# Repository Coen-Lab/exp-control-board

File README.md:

# Experimental Control Board (ECB)
This repository houses the electronics, firmware, and enclosure design for the experimental control board. This board was designed by [Max Hunter](https://maxhunter.me/), to the specifications of Philip Coen. It  is designed both with features that are universally applicable to experimental neuroscience rigs, as well as some features which may not (but may) be useful outside the Coen Lab. In particular, the assembled board can be purchased at a comparable price to a _single component_ from a commercial supplier (e.g. this [current driver](https://www.thorlabs.com/thorproduct.cfm?partnumber=LEDD1B) or this [adjustable photodiode](https://www.thorlabs.com/thorproduct.cfm?partnumber=PDA8A2)). For most applications, this board can fully replace these components (in the enclosure of the current driver, it can replace 3 of them), amongst others.

If purchased directly from Max, the Version 3 board includes:
- 24V, 220W power supply
- Photodiode (2-pin)
- Temperature sensor (3-pin)
- Enclosure (Pink in above images)
- ECB Version 3 with the following features
	- Temperature-controlled PID Peltier cooler output with overheat protection
	- Two fixed 12V, 3A power rails for auxiliary devices, with switchable on/off outputs
	- Four variable 3-24V, 3A power rails for auxiliary devices, with switchable on/off outputs
	- Three adjustable 0-1A continuous current drivers for LEDs or similar devices
	- Photosensor with variable sensitivity trigger (5V TTL digital output)
	- Two DRV104 valve controllers, 12V output
	- One Arduino Nano V3, used to control Peltier output and random ‘flipper’ output, with 6 spare IO for future expansion

For useage instructions, please see:

[Version 3 documentation](Version3/README.md)

To purchase pre-assembled units, including photodiode etc. mentioned above, for ~£450 (at time of writing), please contact [Max Hunter](https://maxhunter.me/). 

All details are open source, and you can alternatively print your own boards: there is a folder of Gerbers and pick 'n place files for each version. However, please be aware that stock levels may necessitate equivalent-part subsitutions, so if you aren't familiar with ordering your own PCBs (e.g. you have no idea what Gerbers and pick 'n place files are), then we _strongly_ recommend you order pre-assembled units. Max may also be able to make minor design changes (for a design fee) if there are particular elements you would like added or removed.

&nbsp;
&nbsp;
This work is licensed under a
[Creative Commons Attribution-NonCommercial-ShareAlike 4.0 International License][cc-by-nc-sa].

[![CC BY-NC-SA 4.0][cc-by-nc-sa-image]][cc-by-nc-sa]

[cc-by-nc-sa]: http://creativecommons.org/licenses/by-nc-sa/4.0/
[cc-by-nc-sa-image]: https://licensebuttons.net/l/by-nc-sa/4.0/88x31.png
[cc-by-nc-sa-shield]: https://img.shields.io/badge/License-CC%20BY--NC--SA%204.0-lightgrey.svg

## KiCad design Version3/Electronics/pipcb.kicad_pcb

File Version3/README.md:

## ECB Version 3 guide and usage instructions

_Above_: Version 3 board CAD file (left) with both top and bottom of enclosure (centre) or just the bottom of the enclosure (right)

Thanks for purchasing (or considering) the ECB Version 3! This guide should act as a basic how-to to get started. If you have any questions/issues please post them on this github so that the entire community can benefit from the answers.

A purchasable Bill of Materials, all source code for the Arduino, a 3D-printable enclosure, and electronics design files can be found in this repository.

The board comes with a one-year warranty against manufacturing defects.

If you have any further questions or have any problems, please leave an issue on this GitHub repository.

## General notes
If purchased directly from Max, you have received:

- 24V, 220W power supply
- Photodiode (2-pin)
- Temperature sensor (3-pin)
- ECB Version 3 with the following features
    - Temperature-controlled PID Peltier cooler output with overheat protection
    - Two fixed 12V, 3A power rails for auxiliary devices, with switchable on/off outputs
    - Four variable 3-24V, 3A power rails for auxiliary devices, with switchable on/off outputs
    - Three adjustable 0-1A continuous current drivers for LEDs or similar devices
    - Photosensor with variable sensitivity trigger (5V TTL digital output)
    - Two DRV104 valve controllers, 12V output
    - One Arduino Nano V3, used to control Peltier output and random ‘flipper’ output, with 6 spare IO for future expansion

Please take the following precautions when handling the board.

* **At no point should you “hot-plug” / screw or unscrew anything into the board when it is powered on. The rapid transients caused by the making/breaking of contacts when screwing a cable in can damage the board as well as any attached components.**
* Do not overload or short-circuit any of the power rails.
* Please pay attention to the total maximum power rating of 220W, which is possible to exceed if fully loading all voltage rails.
* When handling or touching any components on the board, you should ground yourself with an ESD bracelet (£4 on Amazon) or by touching any grounded surface to dissipate electrostatic charge. Humans can accumulate several thousand volts of static charge which will dissipate through the board: several of the components on the board are very sensitive to ESD. When screwing in any of the terminals, take the same precaution, or use an insulated screwdriver so your skin does not make contact with the screw of the terminal.

## Installation/operation instructions

### General notes on screw terminals
All the external connections to the board are made using screw terminals. These accept a wide variety of wire sizes. You should strip 5mm off the wire, then unscrew the terminal until the jaws fully open, insert the wire, and hand-tighten. The screw should clamp down on the conductor (not the insulation) and no conductor should be visible out the end of the connector.

For low-power devices with small cable sizes it is acceptable to insert several wires into a single terminal, as long as they are all sufficiently stripped so that they are making good contact with the terminal.

### Enclosure
Four self-tapping screws can be inserted into the four corners of the enclosure in the pre-drilled holes to mount onto any suitable surface. The board can be installed in any orientation but preferably should be kept away from direct sunlight and heat sources.

### Power in

The board comes with a switchmode 24V, 220W power supply. You should sum up all the power ratings of the various attached devices (including Peltier cooler) and make sure they do not exceed 220W.

Once in the correct position, the insulation on the power connector should be cut off and the ends stripped to 5mm. Slightly twist the copper to make sure no strands splay off, then insert BLACK into ⏚ and RED into +24.

### Power out

There are 6 power rails for auxiliary devices on this board. All of them share the same 3A current rating.

RAIL 1: 12V fixed

RAIL 2: 12V fixed

RAIL 3: Variable 3-23V

RAIL 4: Variable 3-23V

RAIL 5: Variable 3-23V

RAIL 6: Variable 3-23V

RAIL 3-6 are adjustable by turning the potentiometers (blue cuboids) next to the relevant rails with a small insulated flat screwdriver, whilst metering the output voltage with the serial logger on the Arduino, or a multimeter. Care should be taken to make sure the screwdriver does not slip and you do not touch any other components while metering, especially if using a multimeter.

All rails have a GATE input. Leaving this pin disconnected, or connecting this to a voltage below approximately 1.3 V, turns the regulator on, and pulling this pin above 1.3 V (up to a maximum of 25 V) shuts the regulator down. This is a useful feature if you wish to use an Arduino pin (or other logic pin) to switch power to an external component. (Note that there are output capacitors on the voltage rails so the power will not switch off instantly)

### Peltier

This board is tested and designed to work with the following 24V, 60W Peltier cooling module: [https://uk.rs-online.com/web/p/heat-pumps/7777079](https://uk.rs-online.com/web/p/heat-pumps/7777079). Other modules may work, as long as they are 24V and do not exceed 8A.

Insert BLACK into ⏚ and RED into PELT.

Connect overheat switch to any terminal marked ⏚ and OHT (polarity does not matter). This is a NC (normally closed) design which opens if the Peltier overheats - if your Peltier unit does not have an overheat sensor you should either modify the Arduino code or put a small bit of wire between OHT and ⏚ to bypass it.

The temperature sensor (mandatory for Peltier cooling) should be plugged into T SENSOR. Red into +5, yellow into D (data), black into ⏚. It should be positioned close to/underneath the desired position to be kept at a constant temperature.

The two fans (if available) should be plugged into any +12V rail.

The code for the Peltier follows a PID loop with a frequency of approximately 800KHz. It is roughly tuned for The Coen Lab’s original experimental box and so the P, I, D constants may need adjusting if the temperature proves to oscillate or under/overshoot in a new environment or with a different Peltier.

### Photodiode

This is a completely separate module from the rest of the board, designed as an adjustable photodiode trigger at a user-settable light threshold - originally designed to be placed next to a square on a screen to synchronise it with experimental data. This turns a variable light level into a digital 5V TTL logic output. There is a Schmitt trigger to remove hysteresis. The included photodiode (optional) should be plugged with the RED wire into S- and the BLUE wire into S+. The photodiode should be placed in the desired position and the potentiometer adjusted for the desired sensitivity.

The output between OUT and ⏚ is the 5V TTL out. The output between RAW and ⏚ is designed as an ‘analogue backup’ in case the sensitivity is slightly wrong - it is an analogue voltage (controlled by the SENSITIVITY  knob) before the Schmitt comparator where 2.5V is approximately the midpoint threshold.

### Valve drivers

These are 2 completely independent valve drivers. They take 5V TTL logic in (between IN and ⏚) and connect to a valve. The specs are fixed and as follows:

This was designed for the following valve:

225P011-21 ([https://www.nresearch.com/products/valves/pinch-1xnc.html](https://www.nresearch.com/products/valves/pinch-1xnc.html))

When the logic level input goes above approximately 2.2V (maximum 5.5V) the output briefly rises to 12V for 100ms, then continues to pulse between 0V and 12V at a 33% duty cycle until the input voltage drops beneath approximately 1.2V. This keeps the valve open without burning out the solenoid.

### Constant current drivers
\
\

There are 3 constant-current drivers on this board. They are adjustable in 3 fixed steps: 333mA, 667mA, 1000mA, by adding or removing jumpers on the board as shown.

They can also be controlled with the CTL pin for the relevant output as follows:

0-2.5V: scales linearly between 0A and the maximum set current (i.e. if the jumpers are set to 1A, setting the CTL pin at 1.25V will output a target current of 500mA).

2.5-5V: fully ON.

This can be used either as analogue control from 0-2.5V, or as a digital on/off switch by modulating the input voltage between 0 and 5V.

There is an internal pull-up resistor, so leaving this pin floating is the same as pulling it up to +5V (ie "on").

### Arduino I/O
\

This is a breakout board for the included Arduino Nano v3. 

The implemented features in the provided firmware are:

A ‘flipper’ random I/O which randomly flips between HIGH and LOW approximately every 100ms. This is turned on and off by setting FE (flipper enable) to HIGH or LOW.

An OHT overheat sensor for the Peltier (described in the Peltier section above)

Two ⏚ ground terminals and a 5V logic output. This 5V output is a logic reference only and not to be used for power. Drawing more than 50mA of current through it will result in permanent damage to the board. If there is any chance of it shorting to ground (or any other voltage), a 200 ohm resistor in series with it is strongly recommended.

The other outputs match the Arduino pinout and are reserved for future expansion.

Plugging the board into a computer is optional and only needed if you wish to log temperature/rail voltages etc, or update the firmware.

The firmware is available on GitHub and can be modified and uploaded using the connector on the Arduino. Plugging in the USB-C connector and opening up the serial logger on the Arduino app (or a MATLAB/Python program) will print rail voltages and temperature. You can then use the Arduino app to reflash any firmware changes.

## Manufacturing instructions

### Board

A service like JLCPCB can be used with the included Gerber and pick&place files to manufacture and assemble the board.

### Enclosure

Pip Coen has designed a 3D-printable enclosure which can be found in this repository.

The enclosure is designed to take 8 regular M4 nuts and M4 bolts.

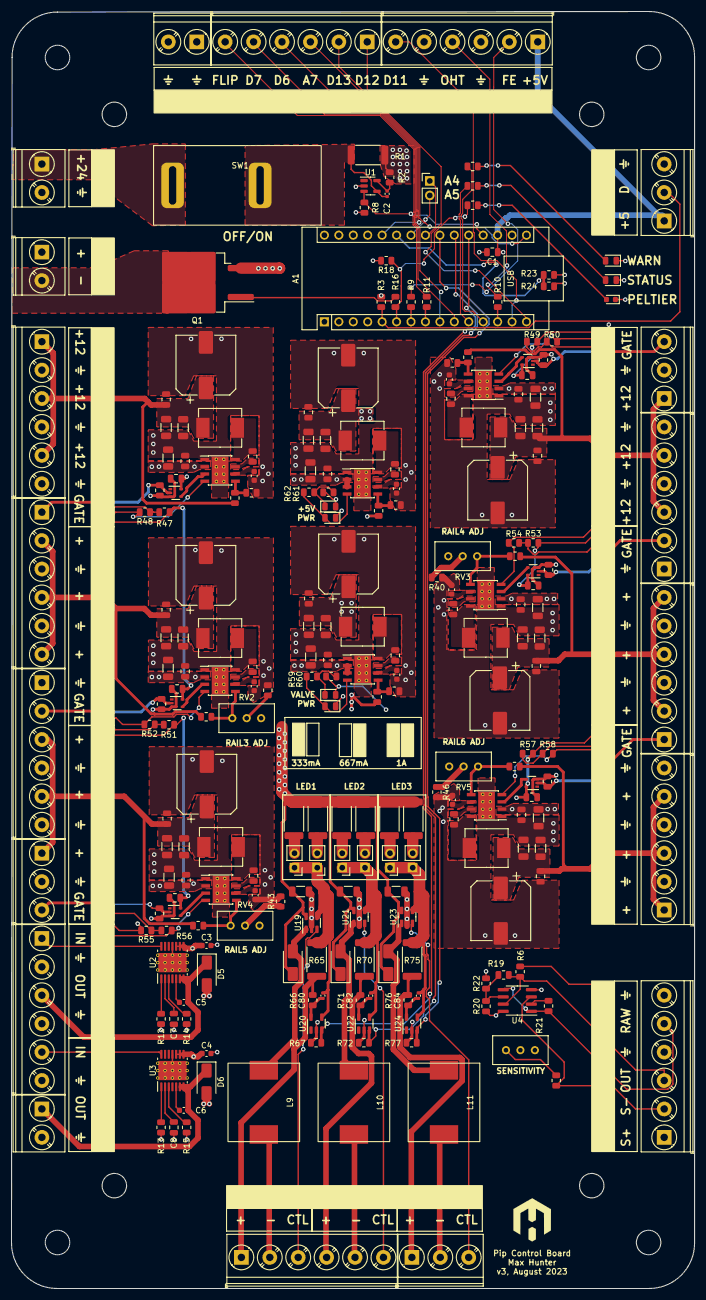
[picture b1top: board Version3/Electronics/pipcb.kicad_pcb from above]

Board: 4 copper layers, 120.2 x 224.7 mm, 272 parts (0 on the bottom side), 148 nets.

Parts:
A1: Arduino_Nano_v3.x; Arduino_Nano
C1, C9, C10, C11, C12, C13, C14, C18, C26, C34, C42, C50, C58, C66, C74: 100n; C_0805_2012Metric
C2, C80, C82, C84: 10p; C_0402_1005Metric
C3, C4, C22, C30, C38, C46, C54, C62, C70, C78: 1u; C_0603_1608Metric
C5, C6: 470p; C_0603_1608Metric
C7, C8: 150n; C_0805_2012Metric
C15, C19, C20, C23, C27, C28, C31, C35, C36, C39, C43, C44, C47, C51, C52, C55, C59, C60, C63, C67, C68, C71, C75, C76, C79, C81, C83: 10u; C_1206_3216Metric
C16, C17, C24, C25, C32, C33, C40, C41, C48, C49, C56, C57, C64, C65, C72, C73: 220n; C_0805_2012Metric
C21, C29, C37, C45, C53, C61, C69, C77: 100u; CP_Elec_10x10
D1, D7, D9, D11, D13, D15, D17, D19, D21: RED; LED_0805_2012Metric
D2: YELLOW; LED_0805_2012Metric
D3, D8, D10, D12, D14, D16, D18, D20, D22: GREEN; LED_0805_2012Metric
D4: BLUE; LED_0603_1608Metric
D5, D6, D23, D24, D25: SS34; D_SMA
G1: LOGO; maxlogo
H1, H2, H3, H4, H5, H6, H7, H8: MountingHole; MountingHole_4.3mm_M4
J1, J2, J4, J5, J7, J8, J12, J14, J15, J17, J19: Conn_01x06; TerminalBlock_Phoenix_PT-1,5-6-5.0-H_1x06_P5.00mm_Horizontal
J3, J6, J16, J18: Conn_01x02; TerminalBlock_Phoenix_PT-1,5-2-5.0-H_1x02_P5.00mm_Horizontal
J9: Conn_01x02; PinHeader_1x02_P2.54mm_Vertical
J10, J11, J13, J20: Conn_01x03; TerminalBlock_Phoenix_PT-1,5-3-5.0-H_1x03_P5.00mm_Horizontal
J21, J22: Conn_01x15; DOT
JP1, JP2, JP3, JP4, JP5, JP6: JUMP; PinHeader_1x02_P2.54mm_Vertical
JP7, JP8, JP9, JP10, JP11, JP12: Jumper_2_Bridged; DOT
L1, L2, L3, L4, L5, L6, L7, L8: 15uH 4A; L_Cenker_CKST0603
L9, L10, L11: 100uH; L_SMMS1360
Q1: LNE08R085; TO-263-2
R1, R65, R70, R75: 0.005R; R_2512_6332Metric
R2, R3, R66, R71, R76: 4.7k; R_0805_2012Metric
R4, R5, R9, R10, R11, R16: 220R; R_0805_2012Metric
R6, R7: 1k; R_0805_2012Metric
R8, R67, R72, R77: 13k; R_0805_2012Metric
R12, R13: 120k; R_0805_2012Metric
R14, R15: 200k; R_0805_2012Metric
R17, R18, R21: 10k; R_0805_2012Metric
R19: 150k; R_0805_2012Metric
R20, R22: 30k; R_0805_2012Metric
R23, R27, R32, R36, R39, R42, R45: 47k 1%; R_0805_2012Metric
R24: 8.87k 1%; R_0805_2012Metric
R25, R28, R30, R33, R35, R38, R41, R44: 100k 1%; R_0805_2012Metric
R26, R29, R31: 9.09k 1%; R_0805_2012Metric
R34: 24.9k 1%; R_0805_2012Metric
R37, R40, R43, R46: 4.3k; R_0805_2012Metric
R47, R49, R51, R53, R55, R57, R59, R61: 470R; R_0805_2012Metric
R48, R50, R52, R54, R56, R58, R60, R62: 560R; R_0805_2012Metric
R63, R68, R73: 0.15R; R_2512_6332Metric
R64, R69, R74: 0.3R; R_2512_6332Metric
RV2, RV3, RV4, RV5: 47k 10-turn; Potentiometer_Bourns_3296W_Vertical
SW1: C3900BAAAA
U1, U20, U22, U24: ZXCT1110; SOT-23-5
U2, U3: DRV104; HTSSOP-14-1EP_4.4x5mm_P0.65mm_EP3.4x5mm_Mask3x3.1mm_Thermal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
U4: MCP6002-xSN; SOIC-8_3.9x4.9mm_P1.27mm
U5, U6, U7, U8, U9, U10: 74LVC1G04; SOT-353_SC-70-5
U11, U12, U13, U14, U15, U16, U17, U18: LMR33630ADDA; Texas_HSOP-8-1EP_3.9x4.9mm_P1.27mm_ThermalVias
U19, U21, U23: AL8861WT-7; TSOT-23-5
locked: 5M; Potentiometer_Bourns_3296W_Vertical

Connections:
5V_PG: D22.2 (A), R62.2, U18.4 (PG)
24_V_ADC: A1.25 (A6), R23.1, R24.2
+24V: C15.1, C16.1, C23.1, C24.1, C31.1, C32.1, C39.1, C40.1, C47.1, C48.1, C55.1, C56.1, C63.1, C64.1, C71.1, C72.1, C79.1, C81.1, C83.1, D23.1 (K), D24.1 (K), D25.1 (K), J6.1, R1.1, R2.2, R23.2, R63.1, R64.1, R68.1, R69.1, R73.1, R74.1, U11.2 (VIN), U12.2 (VIN), U13.2 (VIN), U14.2 (VIN), U15.2 (VIN), U16.2 (VIN), U17.2 (VIN), U17.3 (EN), U18.2 (VIN), U18.3 (EN), U19.5 (VIN), U21.5 (VIN), U23.5 (VIN)
+VDC: J3.1, SW1.1 (A)
/power_rails/5v_pwr/FB: R33.2, R34.1, U18.5 (FB)
/power_rails/rail1/FB: R25.2, R26.1, U11.5 (FB)
/power_rails/rail1/RAIL_EN: U5.4, U11.3 (EN)
/power_rails/rail2/FB: R30.2, R31.1, U12.5 (FB)
/power_rails/rail2/RAIL_EN: U6.4, U12.3 (EN)
/power_rails/rail3/FB: R35.2, RV2.3, U13.5 (FB)
/power_rails/rail3/RAIL_EN: U7.4, U13.3 (EN)
/power_rails/rail4/FB: R38.2, RV3.3, U14.5 (FB)
/power_rails/rail4/RAIL_EN: U8.4, U14.3 (EN)
/power_rails/rail5/FB: R41.2, RV4.3, U15.5 (FB)
/power_rails/rail5/RAIL_EN: U9.4, U15.3 (EN)
/power_rails/rail6/FB: R44.2, RV5.3, U16.5 (FB)
/power_rails/rail6/RAIL_EN: U10.4, U16.3 (EN)
/power_rails/valve_12v_pwr/FB: R28.2, R29.1, U17.5 (FB)
CURRENT_ADC: A1.19 (A0), R8.2, U1.3 (OUT)
FLIPPER_ENABLE: A1.7 (D4), R9.2
FLIPPER_OUT: A1.8 (D5), R11.2
GND: A1.4 (GND), A1.29 (GND), C1.2, C3.2, C4.2, C7.2, C8.2, C9.2, C10.2, C11.2, C12.2, C13.2, C14.2, C15.2, C16.2, C18.2, C19.2, C20.2, C21.2, C22.2, C23.2, C24.2, C26.2, C27.2, C28.2, C29.2, C30.2, C31.2, C32.2, C34.2, C35.2, C36.2, C37.2, C38.2, C39.2, C40.2, C42.2, C43.2, C44.2, C45.2, C46.2, C47.2, C48.2, C50.2, C51.2, C52.2, C53.2, C54.2, C55.2, C56.2, C58.2, C59.2, C60.2, C61.2, C62.2, C63.2, C64.2, C66.2, C67.2, C68.2, C69.2, C70.2, C71.2, C72.2, C74.2, C75.2, C76.2, C77.2, C78.2, C79.2, C81.2, C83.2, D1.1 (K), D2.1 (K), D3.1 (K), D4.1 (K), D5.2 (A), D6.2 (A), D8.1 (K), D10.1 (K), D12.1 (K), D14.1 (K), D16.1 (K), D18.1 (K), D20.1 (K), D22.1 (K), J1.2, J1.4, J1.6, J2.2, J2.4, J2.6, J3.2, J4.3, J4.5, J5.3, J5.5, J7.1, J7.4, J7.6, J8.1, J8.4, J8.6, J10.2, J11.2, J12.4, J12.6, J13.3, J14.2, J14.4, J14.6, J15.3, J15.5, J16.2, J18.1, J18.2, Q1.3 (S), R8.1, R12.2, R13.2, R14.2, R15.2, R18.2, R22.2, R24.1, R26.2, R27.1, R29.2, R31.2, R32.1, R34.2, R36.1, R37.2, R39.1, R40.2, R42.1, R43.2, R45.1, R46.2, R67.1, R72.1, R77.1, U1.2 (GND), U2.11 (GND), U2.15 (PPAD), U3.11 (GND), U3.15 (PPAD), U4.4 (V-), U5.3 (GND), U6.3 (GND), U7.3 (GND), U8.3 (GND), U9.3 (GND), U10.3 (GND), U11.1 (PGND), U11.9 (AGND), U12.1 (PGND), U12.9 (AGND), U13.1 (PGND), U13.9 (AGND), U14.1 (PGND), U14.9 (AGND), U15.1 (PGND), U15.9 (AGND), U16.1 (PGND), U16.9 (AGND), U17.1 (PGND), U17.9 (AGND), U18.1 (PGND), U18.9 (AGND), U19.2 (GND), U20.2 (GND), U21.2 (GND), U22.2 (GND), U23.2 (GND), U24.2 (GND), locked.2, locked.3
GPIO1: A1.14 (D11), J15.6
GPIO2: A1.15 (D12), J17.1
GPIO3: A1.16 (D13), J17.2
GPIO4: A1.26 (A7), J17.3
GPIO5: A1.9 (D6), J17.4
GPIO6: A1.10 (D7), J17.5
LED1_CONTROL: J19.3, U19.3 (VSET)
LED1_CURR: A1.20 (A1), R67.2, U20.3 (OUT)
LED1_OUT+: J19.1, R65.1, R66.2
LED1_OUT-: J19.2, L9.2
LED2_CONTROL: J19.6, U21.3 (VSET)
LED2_CURR: A1.21 (A2), R72.2, U22.3 (OUT)
LED2_OUT+: J19.4, R70.1, R71.2
LED2_OUT-: J19.5, L10.2
LED3_CONTROL: J20.3, U23.3 (VSET)
LED3_CURR: A1.22 (A3), R77.2, U24.3 (OUT)
LED3_OUT+: J20.1, R75.1, R76.2
LED3_OUT-: J20.2, L11.2
LED_STATUS: A1.11 (D8), R5.2
LED_WARNING: A1.12 (D9), R4.2
unnamed: A1.23 (A4), J9.1
unnamed: A1.24 (A5), J9.2
unnamed: D1.2 (A), R4.1
unnamed: D2.2 (A), R5.1
unnamed: D3.2 (A), R6.1
unnamed: D4.2 (A), R7.1
unnamed: D7.1 (K), R47.1, R48.1
unnamed: D9.1 (K), R49.1, R50.1
unnamed: D11.1 (K), R51.1, R52.1
unnamed: D13.1 (K), R53.1, R54.1
unnamed: D15.1 (K), R55.1, R56.1
unnamed: D17.1 (K), R57.1, R58.1
unnamed: D19.1 (K), R59.1, R60.1
unnamed: D21.1 (K), R61.1, R62.1
unnamed: D23.2 (A), L9.1, U19.1 (LX)
unnamed: D24.2 (A), L10.1, U21.1 (LX)
unnamed: D25.2 (A), L11.1, U23.1 (LX)
unnamed: J15.2, R9.1
unnamed: J15.4, R10.1
unnamed: J17.6, R11.1
unnamed: C80.2, JP1.1 (A), JP2.1 (A), R65.2, U19.4 (ISENSE), U20.4 (Vs+)
unnamed: JP1.2 (B), R63.2
unnamed: JP2.2 (B), R64.2
unnamed: C82.2, JP3.1 (A), JP4.1 (A), R70.2, U21.4 (ISENSE), U22.4 (Vs+)
unnamed: JP3.2 (B), R68.2
unnamed: JP4.2 (B), R69.2
unnamed: C84.2, JP5.1 (A), JP6.1 (A), R75.2, U23.4 (ISENSE), U24.4 (Vs+)
unnamed: JP5.2 (B), R73.2
unnamed: JP6.2 (B), R74.2
unnamed: Q1.1 (G), R16.1
unnamed: R17.2, locked.1
unnamed: R37.1, RV2.2
unnamed: R40.1, RV3.2
unnamed: R43.1, RV4.2
unnamed: R46.1, RV5.2
unnamed: C2.2, R1.2, SW1.2 (B), U1.4 (Vs+)
unnamed: C2.1, R2.1, U1.5 (Vs-)
unnamed: C5.2, U2.5 (BOOT)
unnamed: C7.1, U2.2 (DELAY_ADJ)
unnamed: R12.1, U2.1 (DUTY_ADJ)
unnamed: R14.1, U2.3 (OSC_ADJ)
unnamed: C6.2, U3.5 (BOOT)
unnamed: C8.1, U3.2 (DELAY_ADJ)
unnamed: R13.1, U3.1 (DUTY_ADJ)
unnamed: R15.1, U3.3 (OSC_ADJ)
unnamed: R21.2, U4.2 (-)
unnamed: R19.2, R20.2, R22.1, U4.6 (-)
unnamed: C17.2, U11.7 (BOOT)
unnamed: C17.1, L1.1, U11.8 (SW)
unnamed: C22.1, U11.6 (VCC)
unnamed: C25.2, U12.7 (BOOT)
unnamed: C25.1, L2.1, U12.8 (SW)
unnamed: C30.1, U12.6 (VCC)
unnamed: C33.2, U13.7 (BOOT)
unnamed: C33.1, L3.1, U13.8 (SW)
unnamed: C38.1, U13.6 (VCC)
unnamed: C41.2, U14.7 (BOOT)
unnamed: C41.1, L4.1, U14.8 (SW)
unnamed: C46.1, U14.6 (VCC)
unnamed: C49.2, U15.7 (BOOT)
unnamed: C49.1, L5.1, U15.8 (SW)
unnamed: C54.1, U15.6 (VCC)
unnamed: C57.2, U16.7 (BOOT)
unnamed: C57.1, L6.1, U16.8 (SW)
unnamed: C62.1, U16.6 (VCC)
unnamed: C65.2, U17.7 (BOOT)
unnamed: C65.1, L7.1, U17.8 (SW)
unnamed: C70.1, U17.6 (VCC)
unnamed: C73.2, U18.7 (BOOT)
unnamed: C73.1, L8.1, U18.8 (SW)
unnamed: C78.1, U18.6 (VCC)
unnamed: C80.1, R66.1, U20.5 (Vs-)
unnamed: C82.1, R71.1, U22.5 (Vs-)
unnamed: C84.1, R76.1, U24.5 (Vs-)
OVERHEAT: A1.13 (D10), R10.2
PELTIER_CONTROL: A1.6 (D3), R7.2, R16.2, R18.1
PELTIER_OUT: J6.2, Q1.2 (D)
PS_1: A1.18 (AREF), A1.27 (+5V), C1.1, C9.1, C10.1, C11.1, C12.1, C13.1, C14.1, C74.1, C75.1, C76.1, C77.1, D7.2 (A), D9.2 (A), D11.2 (A), D13.2 (A), D15.2 (A), D17.2 (A), D19.2 (A), D21.2 (A), J12.1, J13.1, J15.1, L8.2, R3.1, R20.1, R33.1, R47.2, R49.2, R51.2, R53.2, R55.2, R57.2, R59.2, R61.2, U4.8 (V+), U5.5 (VCC), U6.5 (VCC), U7.5 (VCC), U8.5 (VCC), U9.5 (VCC), U10.5 (VCC)
PS_2: J12.2, R17.1, U4.3 (+)
PS_RAW_OUT: J12.5, R21.1, U4.1, U4.5 (+)
PS_TRIGGER: J12.3, R6.2, R19.1, U4.7
RAIL1+: C18.1, C19.1, C20.1, C21.1, J2.1, J2.3, J2.5, L1.2, R25.1
RAIL1_EN: J5.1, R27.2, U5.2
RAIL1_PG: D8.2 (A), R48.2, U11.4 (PG)
RAIL2+: C26.1, C27.1, C28.1, C29.1, J7.3, J7.5, J10.1, L2.2, R30.1
RAIL2_EN: J10.3, R32.2, U6.2
RAIL2_PG: D10.2 (A), R50.2, U12.4 (PG)
RAIL3+: C34.1, C35.1, C36.1, C37.1, J5.2, J5.4, J5.6, L3.2, R35.1
RAIL3_EN: J8.2, R36.2, U7.2
RAIL3_PG: D12.2 (A), R52.2, U13.4 (PG)
RAIL4+: C42.1, C43.1, C44.1, C45.1, J4.2, J4.4, J4.6, L4.2, R38.1
RAIL4_EN: J7.2, R39.2, U8.2
RAIL4_PG: D14.2 (A), R54.2, U14.4 (PG)
RAIL5+: C50.1, C51.1, C52.1, C53.1, J8.3, J8.5, J11.1, L5.2, R41.1
RAIL5_EN: J11.3, R42.2, U9.2
RAIL5_PG: D16.2 (A), R56.2, U15.4 (PG)
RAIL6+: C58.1, C59.1, C60.1, C61.1, J1.1, J1.3, J1.5, L6.2, R44.1
RAIL6_EN: J4.1, R45.2, U10.2
RAIL6_PG: D18.2 (A), R58.2, U16.4 (PG)
TEMP_SENSOR: A1.5 (D2), J13.2, R3.2
VALVE1_IN: J14.1, U2.14 (INPUT)
VALVE1_OUT: C5.1, D5.1 (K), J14.3, U2.6 (OUT1), U2.7 (OUT2)
VALVE2_IN: J14.5, U3.14 (INPUT)
VALVE2_OUT: C6.1, D6.1 (K), J16.1, U3.6 (OUT1), U3.7 (OUT2)
VALVE_12V: C3.1, C4.1, C66.1, C67.1, C68.1, C69.1, L7.2, R28.1, U2.8 (VPS1), U2.9 (VPS2), U2.10 (+VS), U3.8 (VPS1), U3.9 (VPS2), U3.10 (+VS)
VALVE_PG: D20.2 (A), R60.2, U17.4 (PG)

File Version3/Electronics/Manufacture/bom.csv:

Designator,Footprint,Quantity,Value,LCSC Part #
A1,Arduino_Nano,1,Arduino_Nano_v3.x,
"C1, C10, C11, C12, C13, C14, C18, C26, C34, C42, C50, C58, C66, C74, C9",0805,15,100n,C28233
"C15, C19, C20, C23, C27, C28, C31, C35, C36, C39, C43, C44, C47, C51, C52, C55, C59, C60, C63, C67, C68, C71, C75, C76, C79, C81, C83",1206,27,10u,C13585
"C16, C17, C24, C25, C32, C33, C40, C41, C48, C49, C56, C57, C64, C65, C72, C73",0805,16,220n,C5378
"C2, C80, C82, C84",0402,4,10p,C32949
"C21, C29, C37, C45, C53, C61, C69, C77",CP_Elec_10x10,8,100u,C371283
"C22, C3, C30, C38, C4, C46, C54, C62, C70, C78",0603,10,1u,C15849
"C5, C6",0603,2,470p,C1620
"C7, C8",0805,2,150n,C408124
"D1, D11, D13, D15, D17, D19, D21, D7, D9",0805,9,RED,C84256
"D10, D12, D14, D16, D18, D20, D22, D3, D8",0805,9,GREEN,C2297
D2,0805,1,YELLOW,C2296
"D23, D24, D25, D5, D6",D_SMA,5,SS34,C8678
D4,0603,1,BLUE,C72041
G1,maxlogo,1,LOGO,
"H1, H2, H3, H4, H5, H6, H7, H8",MountingHole_4.3mm_M4,8,MountingHole,
"J1, J12, J14, J15, J17, J19, J2, J4, J5, J7, J8","TerminalBlock_Phoenix_PT-1,5-6-5.0-H_1x06_P5.00mm_Horizontal",11,Conn_01x06,C192771
"J10, J11, J13, J20","TerminalBlock_Phoenix_PT-1,5-3-5.0-H_1x03_P5.00mm_Horizontal",4,Conn_01x03,C8270
"J16, J18, J3, J6","TerminalBlock_Phoenix_PT-1,5-2-5.0-H_1x02_P5.00mm_Horizontal",4,Conn_01x02,C8269
"J21, J22",DOT,2,Conn_01x15,C2897378
J9,PinHeader_1x02_P2.54mm_Vertical,1,Conn_01x02,
"JP1, JP2, JP3, JP4, JP5, JP6",PinHeader_1x02_P2.54mm_Vertical,6,JUMP,C5116481
"JP10, JP11, JP12, JP7, JP8, JP9",DOT,6,Jumper_2_Bridged,C5305
"L1, L2, L3, L4, L5, L6, L7, L8",L_Cenker_CKST0603,8,15uH 4A,C3002650
"L10, L11, L9",L_SMMS1360,3,100uH,C149534
Q1,TO-263-2,1,LNE08R085,C483709
"R1, R65, R70, R75",2512,4,0.005R,C5121085
"R10, R11, R16, R4, R5, R9",0805,6,220R,C17557
"R12, R13",0805,2,120k,C17436
"R14, R15",0805,2,200k,C17539
"R17, R18, R21",0805,3,10k,C17414
R19,0805,1,150k,C17470
"R2, R3, R66, R71, R76",0805,5,4.7k,C17673
"R20, R22",0805,2,30k,C17621
"R23, R27, R32, R36, R39, R42, R45",0805,7,47k 1%,C17713
R24,0805,1,8.87k 1%,C37551
"R25, R28, R30, R33, R35, R38, R41, R44",0805,8,100k 1%,C149504
"R26, R29, R31",0805,3,9.09k 1%,C408923
R34,0805,1,24.9k 1%,C234872
"R37, R40, R43, R46",0805,4,4.3k,C204496
"R47, R49, R51, R53, R55, R57, R59, R61",0805,8,470R,C17710
"R48, R50, R52, R54, R56, R58, R60, R62",0805,8,560R,C28636
"R6, R7",0805,2,1k,C17513
"R63, R68, R73",2512,3,0.15R,C2924565
"R64, R69, R74",2512,3,0.3R,C2912677
"R67, R72, R77, R8",0805,4,13k,C217812
RV1,Potentiometer_Bourns_3296W_Vertical,1,5M,C780121
"RV2, RV3, RV4, RV5",Potentiometer_Bourns_3296W_Vertical,4,47k 10-turn,C83686
SW1,C3900BAAAA,1,C3900BAAAA,C4949944
"U1, U20, U22, U24",SOT-23-5,4,ZXCT1110,C78482
"U10, U5, U6, U7, U8, U9",SOT-353_SC-70-5,6,74LVC1G04,C8207
"U11, U12, U13, U14, U15, U16, U17, U18",Texas_HSOP-8-1EP_3.9x4.9mm_P1.27mm_ThermalVias,8,LMR33630ADDA,C841384
"U19, U21, U23",TSOT-23-5,3,AL8861WT-7,C581338
"U2, U3",HTSSOP-14-1EP_4.4x5mm_P0.65mm_EP3.4x5mm_Mask3x3.1mm_ThermalVias,2,DRV104,C1556572
U4,SOIC-8_3.9x4.9mm_P1.27mm,1,MCP6002-xSN,C7377

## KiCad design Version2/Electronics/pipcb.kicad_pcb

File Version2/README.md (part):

## PipCB v2 assembly and usage instructions

### Max Hunter, March 2024

Thanks for purchasing a PipCB! This guide should act as a basic how-to to get started.

A purchasable Bill of Materials, all source code for the Arduino, and electronics design files can be found in this repository.

The board comes with a one-year warranty against manufacturing defects.

If you have any further questions or have any problems, please leave an issue on this GitHub repository.

## General notes

This board was designed by [Max Hunter](https://maxhunter.me/), to the specifications of Philip Coen. It  is designed both with features that are universally applicable to experimental neuroscience rigs, as well as some features which may not (but may) be useful outside the Coen Lab. In particular, the entire board costs less than the commercial equivalent of some single features (e.g. constant current delivery, or a thresholded, adjustable photodiode circuit).

The board as sold comprises:

- 24V, 220W power supply
- Photodiode (2-pin)
- Temperature sensor (3-pin)
- Enclosure
- ECB Version 2 with the following features
    - Temperature-controlled PID Peltier cooler output with overheat protection
    - Two fixed 12V, 3A power rails for auxiliary devices, with switchable on/off outputs
    - Four variable 3-24V, 3A power rails for auxiliary devices, with switchable on/off outputs
    - Two adjustable 0-1A continuous current drivers for LEDs or similar devices
    - Photosensor with variable sensitivity trigger (5V TTL digital output)
    - Three DRV104 valve controllers, 12V output
    - One Arduino Nano V3, used to control Peltier output and random ‘flipper’ output, with 6 spare IO for future expansion

Please take the following precautions when handling the board.

* **At no point should you “hot-plug” / screw or unscrew anything into the board when it is powered on. The rapid transients caused by the making/breaking of contacts when screwing a cable in can damage the board as well as any attached components.**
* Do not overload or short-circuit any of the power rails.
* Please pay attention to the total maximum current rating of 220W, which is possible to exceed if fully loading all voltage rails.
* When handling or touching any components on the board, you should ground yourself with an ESD bracelet (£4 on Amazon) or by touching any grounded surface to dissipate electrostatic charge. Humans can accumulate several thousand volts of static charge which will dissipate through the board: several of the components on the board are very sensitive to ESD. When screwing in any of the terminals, take the same precaution, or use an insulated screwdriver so your skin does not make contact with the screw of the terminal.

## Installation/operation instructions

### General notes on screw terminals

All the external connections to the board are made using screw terminals. These accept a wide variety of wire sizes. You should strip 5mm off the wire, then unscrew the terminal until the jaws fully open, insert the wire, and hand-tighten. The screw should clamp down on the conductor (not the insulation) and no conductor should be visible out the end of the connector.

For low-power devices with small cable sizes it is acceptable to insert several wires into a single terminal, as long as they are all sufficiently stripped so that they are making good contact with the terminal.

### Case

Four self-tapping screws can be inserted into the four corners of the case in the pre-drilled holes to mount onto any suitable surface. The board can be installed in any orientation but preferably should be kept away from direct sunlight and heat sources.

### Power in

The board comes with a switchmode 24V, 220W power supply. You should sum up all the current ratings of the various attached devices (including Peltier cooler) and make sure they do not exceed 220W.

Once in the correct position, the insulation on the power connector should be cut off and the ends stripped to 5mm. Slightly twist the copper to make sure no strands splay off, then insert BLACK into ⏚ and RED into +24.

### Power out

There are 6 power rails for auxiliary devices on this board. All of them share the same 3A current rating.

RAIL 1: 12V fixed

RAIL 2: 12V fixed

RAIL 3: Variable 3-23V

RAIL 4: Variable 3-23V

RAIL 5: Variable 3-23V

RAIL 6: Variable 3-23V

RAIL 3-6 are adjustable by turning the potentiometers next to the relevant rails with a small insulated flat screwdriver, whilst metering the output voltage with the serial logger on the Arduino, or a multimeter. Care should be taken to make sure the screwdriver does not slip and you do not touch any other components while metering, especially if using a multimeter.

All rails have a GATE input. Leaving this pin disconnected, or connecting this to a voltage below approximately 1.3 V, turns the regulator on, and pulling this pin above 1.3 V (up to a maximum of 25 V) shuts the regulator down. This is a useful feature if you wish to use an Arduino pin (or other logic pin) to switch power to an external component. (Note that there are output capacitors on the voltage rails so the power will not switch off instantly)

### Peltier

This board is tested and designed to work with the following 24V, 60W Peltier cooling module: [https://uk.rs-online.com/web/p/heat-pumps/7777079](https://uk.rs-online.com/web/p/heat-pumps/7777079). Other modules may work, as long as they are 24V and do not exceed 8A.

Insert BLACK into ⏚ and RED into PELT.

Connect overheat switch to any terminal marked ⏚ and OHT (polarity doesn’t matter). This is a NC (normally closed) design which opens if the Peltier overheats - if your Peltier unit does not have an overheat sensor you should either modify the Arduino code or put a small bit of wire between OHT and ⏚ to bypass it.

The temperature sensor (mandatory for Peltier cooling) should be plugged into T SENSOR. Red into +5, yellow into D (data), black into ⏚. It should be positioned close to/underneath the desired position to be kept at a constant temperature.

The two fans (if available) should be plugged into any +12V rail.

The code for the Peltier follows a PID loop with a frequency of approximately 800KHz. It is roughly tuned for Pip’s original experimental box and so the P, I, D constants may need adjusting if the temperature proves to oscillate or under/overshoot in a new environment or with a different Peltier.

### Photodiode

This is a completely separate module from the rest of the board, designed as an adjustable photodiode trigger at a user-settable light threshold - originally designed to be placed next to a square on a screen to synchronise it with experimental data. This turns a variable light level into a digital 5V TTL logic output. There is a Schmitt trigger to remove hysteresis. The included photodiode (optional) should be plugged with the RED wire into S- and the BLUE wire into S+. The photodiode should be placed in the desired position and the potentiometer adjusted for the desired sensitivity.

The output between OUT and ⏚ is the 5V TTL out. The output between RAW and ⏚ is designed as an ‘analogue backup’ in case the sensitivity is slightly wrong - it is an analogue voltage (controlled by the SENSITIVITY  knob) before the Schmitt comparator where 2.5V is approximately the midpoint threshold.

### Valve drivers

These are 3 completely independent valve drivers. They take 5V TTL logic in (between IN and ⏚) and connect to a valve. The specs are fixed and as follows:

This was designed for the following valve:

225P011-21 ([https://www.nresearch.com/products/valves/pinch-1xnc.html](https://www.nresearch.com/products/valves/pinch-1xnc.html))

When the logic level input goes above approximately 2.2V (maximum 5.5V) the output briefly rises to 12V for 100ms, then continues to pulse between 0V and 12V at a 33% duty cycle until the input voltage drops beneath approximately 1.2V. This keeps the valve open without burning out the solenoid.

### Constant current drivers

There are 2 constant-current drivers on this board. They are adjustable in 3 fixed steps: 333mA, 667mA, 1000mA, by adding or removing jumpers on the board as shown.

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
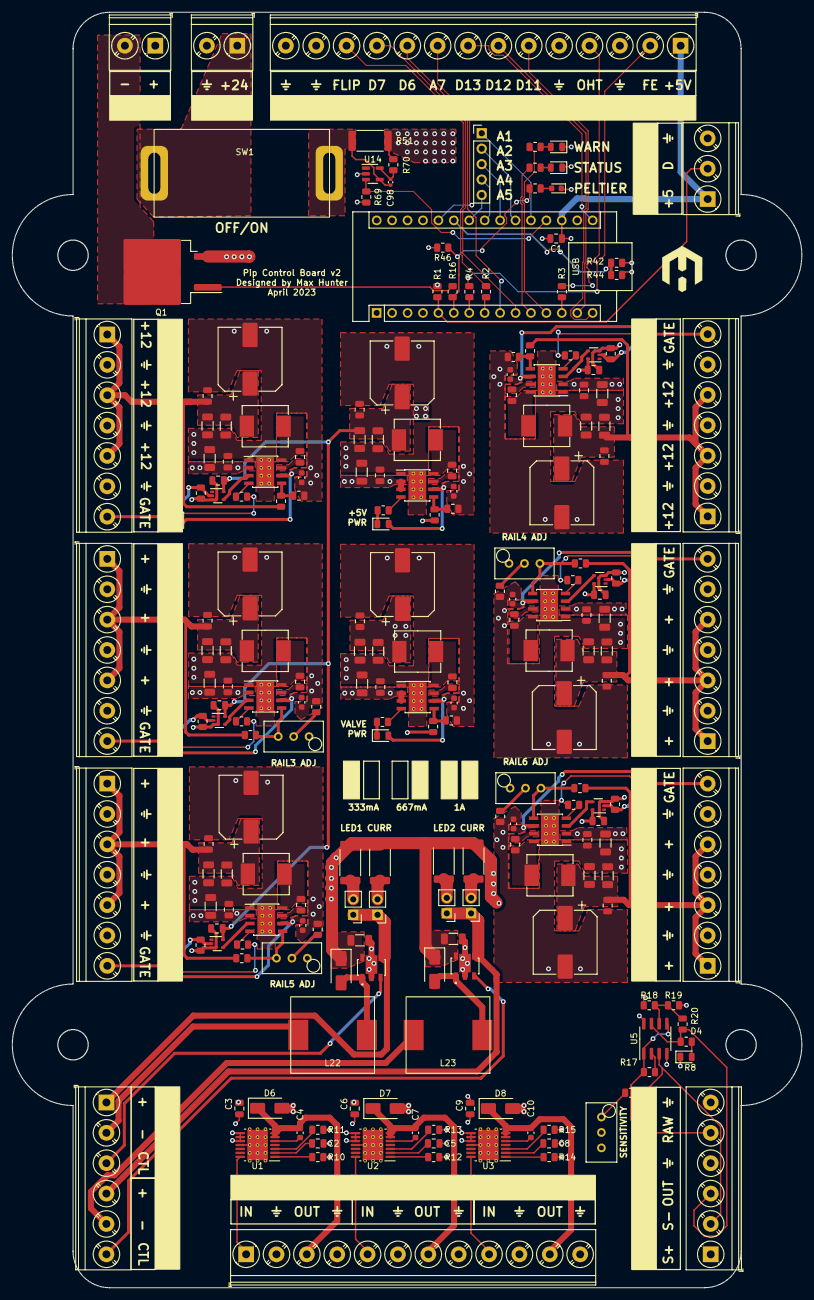
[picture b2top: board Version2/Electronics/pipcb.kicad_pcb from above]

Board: 4 copper layers, 130.0 x 210.0 mm, 217 parts (0 on the bottom side), 142 nets.

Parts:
A1: Arduino_Nano_v3.x; Arduino_Nano
C1, C11, C12, C13, C14, C15, C16, C38, C45, C53, C61, C69, C77, C85, C93: 100n; C_0805_2012Metric
C2, C5, C8: 150n; C_0805_2012Metric
C3, C6, C9: 1u; C_0805_2012Metric
C4, C7, C10: 470p; C_0603_1608Metric
C32, C33, C37, C39, C40, C42, C46, C47, C50, C54, C55, C58, C62, C63, C66, C70, C71, C74, C78, C79, C82, C86, C87, C90, C94, C95: 10u; C_1206_3216Metric
C34, C36, C43, C44, C51, C52, C59, C60, C67, C68, C75, C76, C83, C84, C91, C92: 220n; C_0805_2012Metric
C35, C49, C57, C65, C73, C81, C89, C97: 1u; C_0603_1608Metric
C98: 10p; C_0402_1005Metric
C99, C100, C101, C102, C103, C104, C105, C106: 100u; CP_Elec_10x10
D1, D9, D10, D11, D12, D13, D14, D15: PG; LED_0805_2012Metric
D2: RED; LED_0805_2012Metric
D3: YELLOW; LED_0805_2012Metric
D4: GREEN; LED_0805_2012Metric
D5: BLUE; LED_0603_1608Metric
D6, D7, D8, D16, D17: SS34; D_SMA
J1: PWR; TerminalBlock_Phoenix_PT-1,5-2-5.0-H_1x02_P5.00mm_Horizontal
J2: RAIL1; TerminalBlock_Phoenix_PT-1,5-7-5.0-H_1x07_P5.00mm_Horizontal
J3: RAIL2; TerminalBlock_Phoenix_PT-1,5-7-5.0-H_1x07_P5.00mm_Horizontal
J4: RAIL3; TerminalBlock_Phoenix_PT-1,5-7-5.0-H_1x07_P5.00mm_Horizontal
J5: RAIL4; TerminalBlock_Phoenix_PT-1,5-7-5.0-H_1x07_P5.00mm_Horizontal
J6: RAIL5; TerminalBlock_Phoenix_PT-1,5-7-5.0-H_1x07_P5.00mm_Horizontal
J7: RAIL6; TerminalBlock_Phoenix_PT-1,5-7-5.0-H_1x07_P5.00mm_Horizontal
J8: ARDUINO; TerminalBlock_Phoenix_PT-1,5-14-5.0-H_1x14_P5.00mm_Horizont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
J9: LED; TerminalBlock_Phoenix_PT-1,5-6-5.0-H_1x06_P5.00mm_Horizontal
J10: TEMP_SENSOR; TerminalBlock_Phoenix_PT-1,5-3-5.0-H_1x03_P5.00mm_Horizontal
J11: VALVES; TerminalBlock_Phoenix_PT-1,5-12-5.0-H_1x12_P5.00mm_Horizont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
J12: PHOTOSENSOR; TerminalBlock_Phoenix_PT-1,5-6-5.0-H_1x06_P5.00mm_Horizontal
J13: PELTIER; TerminalBlock_Phoenix_PT-1,5-2-5.0-H_1x02_P5.00mm_Horizontal
J14: GPIO_INT; PinHeader_1x05_P2.54mm_Vertical
JP1, JP2, JP3, JP4: JUMP; PinHeader_1x02_P2.54mm_Vertical
L14, L15, L16, L17, L18, L19, L20, L21: 15uH 4A; L_Cenker_CKST0603
L22, L23: 100uH; L_SMMS1360
Q1: LNE08R085; TO-263-2
R1, R54, R56, R58, R60, R70: 4.7k; R_0805_2012Metric
R2, R3, R4, R5, R6, R7, R16, R21, R22, R23, R24, R25, R26, R27: 220R; R_0805_2012Metric
R8, R9: 1K; R_0805_2012Metric
R10, R12, R14: 120k; R_0805_2012Metric
R11, R13, R15: 200k; R_0805_2012Metric
R17, R46, R47: 10K; R_0805_2012Metric
R18, R19: 30k; R_0805_2012Metric
R20: 150k; R_0805_2012Metric
R28, R29, R30, R31, R32, R33, R42: 47k 1%; R_0805_2012Metric
R44: 8.87k 1%; R_0805_2012Metric
R48, R50, R53, R55, R57, R59, R61, R63: 100k 1%; R_0805_2012Metric
R49, R52, R62: 9.09k 1%; R_0805_2012Metric
R51: 0.005R; R_2512_6332Metric
R64: 24.9k 1%; R_0805_2012Metric
R65, R66: 0.15R; R_2512_6332Metric
R67, R68: 0.3R; R_2512_6332Metric
R69: 13k; R_0805_2012Metric
RV1: 5M; Potentiometer_Bourns_3296W_Vertical
RV6, RV7, RV8, RV9: 47k 10-turn; Potentiometer_Bourns_3296W_Vertical
SW1: RS 206-6972; RS 2066972
U1, U2, U3: DRV104; HTSSOP-14-1EP_4.4x5mm_P0.65mm_EP3.4x5mm_Mask3x3.1mm_Thermal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
U4, U15, U16, U17, U18, U19, U20, U21: LMR33630ADDA; Texas_HSOP-8-1EP_3.9x4.9mm_P1.27mm_ThermalVias
U5: MCP6002-xSN; SOIC-8_3.9x4.9mm_P1.27mm
U6, U7, U8, U9, U10, U11: 74LVC1G04; SOT-353_SC-70-5
U13, U22: AL8861Y-13; CONV_AL8861Y-13
U14: ZXCT1110; SOT-23-5

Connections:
5V_PG: R27.1, U21.4 (PG)
24_V_ADC: A1.25 (A6), R42.1, R44.2
+24V: C32.1, C33.1, C34.1, C37.1, C42.1, C43.1, C50.1, C51.1, C58.1, C59.1, C66.1, C67.1, C74.1, C75.1, C82.1, C83.1, C90.1, C91.1, D16.1 (K), D17.1 (K), J13.1, R42.2, R51.1, R65.1, R66.1, R67.1, R68.1, R70.2, U4.2 (VIN), U13.5 (VIN), U15.2 (VIN), U16.2 (VIN), U17.2 (VIN), U18.2 (VIN), U19.2 (VIN), U20.2 (VIN), U20.3 (EN), U21.2 (VIN), U21.3 (EN), U22.5 (VIN)
+VDC: J1.1, SW1.1 (A)
/power_rails/5v_pwr/FB: R63.2, R64.1, U21.5 (FB)
/power_rails/rail1/FB: R48.2, R49.1, U4.5 (FB)
/power_rails/rail1/RAIL_EN: U4.3 (EN), U6.4
/power_rails/rail2/FB: R50.2, R52.1, U15.5 (FB)
/power_rails/rail2/RAIL_EN: U7.4, U15.3 (EN)
/power_rails/rail3/FB: R55.2, RV6.3, U16.5 (FB)
/power_rails/rail3/RAIL_EN: U8.4, U16.3 (EN)
/power_rails/rail4/FB: R53.2, RV7.3, U17.5 (FB)
/power_rails/rail4/RAIL_EN: U9.4, U17.3 (EN)
/power_rails/rail5/FB: R57.2, RV8.3, U18.5 (FB)
/power_rails/rail5/RAIL_EN: U10.4, U18.3 (EN)
/power_rails/rail6/FB: R59.2, RV9.3, U19.5 (FB)
/power_rails/rail6/RAIL_EN: U11.4, U19.3 (EN)
/power_rails/valve_12v_pwr/FB: R61.2, R62.1, U20.5 (FB)
CURRENT_ADC: A1.19 (A0), R69.2, U14.3 (OUT)
FLIPPER_ENABLE: A1.7 (D4), R4.2
FLIPPER_OUT: A1.8 (D5), R2.2
GND: A1.4 (GND), A1.29 (GND), C1.2, C2.2, C3.2, C5.2, C6.2, C8.2, C9.2, C11.2, C12.2, C13.2, C14.2, C15.2, C16.2, C32.2, C33.2, C34.2, C35.2, C37.2, C38.2, C39.2, C40.2, C42.2, C43.2, C45.2, C46.2, C47.2, C49.2, C50.2, C51.2, C53.2, C54.2, C55.2, C57.2, C58.2, C59.2, C61.2, C62.2, C63.2, C65.2, C66.2, C67.2, C69.2, C70.2, C71.2, C73.2, C74.2, C75.2, C77.2, C78.2, C79.2, C81.2, C82.2, C83.2, C85.2, C86.2, C87.2, C89.2, C90.2, C91.2, C93.2, C94.2, C95.2, C97.2, C99.2, C100.2, C101.2, C102.2, C103.2, C104.2, C105.2, C106.2, D2.1 (K), D3.1 (K), D4.1 (K), D5.1 (K), D6.2 (A), D7.2 (A), D8.2 (A), J1.2, J2.2, J2.4, J2.6, J3.2, J3.4, J3.6, J4.2, J4.4, J4.6, J5.2, J5.4, J5.6, J6.2, J6.4, J6.6, J7.2, J7.4, J7.6, J8.3, J8.5, J8.13, J8.14, J10.3, J11.2, J11.4, J11.6, J11.8, J11.10, J11.12, J12.4, J12.6, Q1.3 (S), R10.2, R11.2, R12.2, R13.2, R14.2, R15.2, R19.2, R28.1, R29.1, R30.1, R31.1, R32.1, R33.1, R44.1, R46.2, R49.2, R52.2, R54.2, R56.2, R58.2, R60.2, R62.2, R64.2, R69.1, RV1.2, RV1.3, U1.11 (GND), U1.15 (PPAD), U2.11 (GND), U2.15 (PPAD), U3.11 (GND), U3.15 (PPAD), U4.1 (PGND), U4.9 (AGND), U5.4 (V-), U6.3 (GND), U7.3 (GND), U8.3 (GND), U9.3 (GND), U10.3 (GND), U11.3 (GND), U13.2 (GND), U14.2 (GND), U15.1 (PGND), U15.9 (AGND), U16.1 (PGND), U16.9 (AGND), U17.1 (PGND), U17.9 (AGND), U18.1 (PGND), U18.9 (AGND), U19.1 (PGND), U19.9 (AGND), U20.1 (PGND), U20.9 (AGND), U21.1 (PGND), U21.9 (AGND), U22.2 (GND)
GPIO1: A1.14 (D11), J8.6
GPIO2: A1.15 (D12), J8.7
GPIO3: A1.16 (D13), J8.8
GPIO4: A1.26 (A7), J8.9
GPIO5: A1.9 (D6), J8.10
GPIO6: A1.10 (D7), J8.11
LED1_CONTROL: J9.3, U13.3 (VSET)
LED1_OUT+: J9.1, JP1.1 (A), JP2.1 (A), U13.4 (ISENSE)
LED1_OUT-: J9.2, L22.2
LED2_CONTROL: J9.6, U22.3 (VSET)
LED2_OUT+: J9.4, JP3.1 (A), JP4.1 (A), U22.4 (ISENSE)
LED2_OUT-: J9.5, L23.2
LED_STATUS: A1.11 (D8), R7.2
LED_WARNING: A1.12 (D9), R6.2
unnamed: A1.20 (A1), J14.1
unnamed: A1.21 (A2), J14.2
unnamed: A1.22 (A3), J14.3
unnamed: A1.23 (A4), J14.4
unnamed: A1.24 (A5), J14.5
unnamed: C35.1, D1.2 (A), U4.6 (VCC)
unnamed: D1.1 (K), R5.2
unnamed: D2.2 (A), R6.1
unnamed: D3.2 (A), R7.1
unnamed: D4.2 (A), R8.1
unnamed: D5.2 (A), R9.1
unnamed: C49.1, D9.2 (A), U15.6 (VCC)
unnamed: D9.1 (K), R21.2
unnamed: C57.1, D10.2 (A), U16.6 (VCC)
unnamed: D10.1 (K), R22.2
unnamed: C65.1, D11.2 (A), U17.6 (VCC)
unnamed: D11.1 (K), R23.2
unnamed: C73.1, D12.2 (A), U18.6 (VCC)
unnamed: D12.1 (K), R24.2
unnamed: C81.1, D13.2 (A), U19.6 (VCC)
unnamed: D13.1 (K), R25.2
unnamed: C89.1, D14.2 (A), U20.6 (VCC)
unnamed: D14.1 (K), R26.2
unnamed: C97.1, D15.2 (A), U21.6 (VCC)
unnamed: D15.1 (K), R27.2
unnamed: D16.2 (A), L23.1, U22.1 (LX)
unnamed: D17.2 (A), L22.1, U13.1 (LX)
unnamed: J8.2, R4.1
unnamed: J8.4, R3.1
unnamed: J8.12, R2.1
unnamed: JP1.2 (B), R66.2
unnamed: JP2.2 (B), R67.2
unnamed: JP3.2 (B), R65.2
unnamed: JP4.2 (B), R68.2
unnamed: Q1.1 (G), R16.1
unnamed: R47.2, RV1.1
unnamed: R54.1, RV7.2
unnamed: R56.1, RV6.2
unnamed: R58.1, RV8.2
unnamed: R60.1, RV9.2
unnamed: C98.2, R51.2, SW1.2 (B), U14.4 (Vs+)
unnamed: C4.2, U1.5 (BOOT)
unnamed: C2.1, U1.2 (DELAY_ADJ)
unnamed: R10.1, U1.1 (DUTY_ADJ)
unnamed: R11.1, U1.3 (OSC_ADJ)
unnamed: C7.2, U2.5 (BOOT)
unnamed: C5.1, U2.2 (DELAY_ADJ)
unnamed: R12.1, U2.1 (DUTY_ADJ)
unnamed: R13.1, U2.3 (OSC_ADJ)
unnamed: C10.2, U3.5 (BOOT)
unnamed: C8.1, U3.2 (DELAY_ADJ)
unnamed: R14.1, U3.1 (DUTY_ADJ)
unnamed: R15.1, U3.3 (OSC_ADJ)
unnamed: C36.2, U4.7 (BOOT)
unnamed: C36.1, L14.1, U4.8 (SW)
unnamed: R17.2, U5.2 (-)
unnamed: R18.2, R19.1, R20.2, U5.6 (-)
unnamed: C98.1, R70.1, U14.5 (Vs-)
unnamed: C44.2, U15.7 (BOOT)
unnamed: C44.1, L15.1, U15.8 (SW)
unnamed: C52.2, U16.7 (BOOT)
unnamed: C52.1, L16.1, U16.8 (SW)
unnamed: C60.2, U17.7 (BOOT)
unnamed: C60.1, L17.1, U17.8 (SW)
unnamed: C68.2, U18.7 (BOOT)
unnamed: C68.1, L18.1, U18.8 (SW)
unnamed: C76.2, U19.7 (BOOT)
unnamed: C76.1, L19.1, U19.8 (SW)
unnamed: C84.2, U20.7 (BOOT)
unnamed: C84.1, L20.1, U20.8 (SW)
unnamed: C92.2, U21.7 (BOOT)
unnamed: C92.1, L21.1, U21.8 (SW)
OVERHEAT: A1.13 (D10), R3.2
PELTIER_CONTROL: A1.6 (D3), R9.2, R16.2, R46.1
PELTIER_OUT: J13.2, Q1.2 (D)
PS_1: A1.18 (AREF), A1.27 (+5V), C1.1, C11.1, C12.1, C13.1, C14.1, C15.1, C16.1, C93.1, C94.1, C95.1, C106.1, J8.1, J10.1, J12.1, L21.2, R1.1, R18.1, R63.1, U5.8 (V+), U6.5 (VCC), U7.5 (VCC), U8.5 (VCC), U9.5 (VCC), U10.5 (VCC), U11.5 (VCC)
PS_2: J12.2, R47.1, U5.3 (+)
PS_RAW_OUT: J12.5, R17.1, U5.1, U5.5 (+)
PS_TRIGGER: J12.3, R8.2, R20.1, U5.7
RAIL1+: C38.1, C39.1, C40.1, C99.1, J2.1, J2.3, J2.5, L14.2, R48.1
RAIL1_EN: J2.7, R28.2, U6.2
RAIL1_PG: R5.1, U4.4 (PG)
RAIL2+: C45.1, C46.1, C47.1, C100.1, J3.1, J3.3, J3.5, L15.2, R50.1
RAIL2_EN: J3.7, R29.2, U7.2
RAIL2_PG: R21.1, U15.4 (PG)
RAIL3+: C53.1, C54.1, C55.1, C101.1, J4.1, J4.3, J4.5, L16.2, R55.1
RAIL3_EN: J4.7, R30.2, U8.2
RAIL3_PG: R22.1, U16.4 (PG)
RAIL4+: C61.1, C62.1, C63.1, C102.1, J5.1, J5.3, J5.5, L17.2, R53.1
RAIL4_EN: J5.7, R31.2, U9.2
RAIL4_PG: R23.1, U17.4 (PG)
RAIL5+: C69.1, C70.1, C71.1, C103.1, J6.1, J6.3, J6.5, L18.2, R57.1
RAIL5_EN: J6.7, R32.2, U10.2
RAIL5_PG: R24.1, U18.4 (PG)
RAIL6+: C77.1, C78.1, C79.1, C104.1, J7.1, J7.3, J7.5, L19.2, R59.1
RAIL6_EN: J7.7, R33.2, U11.2
RAIL6_PG: R25.1, U19.4 (PG)
TEMP_SENSOR: A1.5 (D2), J10.2, R1.2
VALVE1_IN: J11.1, U1.14 (INPUT)
VALVE1_OUT: C4.1, D6.1 (K), J11.3, U1.6 (OUT1), U1.7 (OUT2)
VALVE2_IN: J11.5, U2.14 (INPUT)
VALVE2_OUT: C7.1, D7.1 (K), J11.7, U2.6 (OUT1), U2.7 (OUT2)
VALVE3_IN: J11.9, U3.14 (INPUT)
VALVE3_OUT: C10.1, D8.1 (K), J11.11, U3.6 (OUT1), U3.7 (OUT2)
VALVE_12V: C3.1, C6.1, C9.1, C85.1, C86.1, C87.1, C105.1, L20.2, R61.1, U1.8 (VPS1), U1.9 (VPS2), U1.10 (+VS), U2.8 (VPS1), U2.9 (VPS2), U2.10 (+VS), U3.8 (VPS1), U3.9 (VPS2), U3.10 (+VS)
VALVE_PG: R26.1, U20.4 (PG)

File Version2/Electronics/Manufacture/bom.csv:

Designator,Footprint,Quantity,Value,LCSC Part #
A1,Arduino_Nano,1,Arduino_Nano_v3.x,
"C1, C11, C12, C13, C14, C15, C16, C38, C45, C53, C61, C69, C77, C85, C93",0805,15,100n,C28233
"C10, C4, C7",0603,3,470p,C1620
"C100, C101, C102, C103, C104, C105, C106, C99",CP_Elec_10x10,8,100u,C371283
"C2, C5, C8",0805,3,150n,C376934
"C3, C6, C9",0805,3,1u,C28323
"C32, C33, C37, C39, C40, C42, C46, C47, C50, C54, C55, C58, C62, C63, C66, C70, C71, C74, C78, C79, C82, C86, C87, C90, C94, C95",1206,26,10u,C13585
"C34, C36, C43, C44, C51, C52, C59, C60, C67, C68, C75, C76, C83, C84, C91, C92",0805,16,220n,C5378
"C35, C49, C57, C65, C73, C81, C89, C97",0603,8,1u,C15849
C98,0402,1,10p,C32949
"D1, D10, D11, D12, D13, D14, D15, D9",0805,8,PG,C2297
"D16, D17, D6, D7, D8",D_SMA,5,SS34,C8678
D2,0805,1,RED,C84256
D3,0805,1,YELLOW,C2296
D4,0805,1,GREEN,C2297
D5,0603,1,BLUE,C72041
J1,"TerminalBlock_Phoenix_PT-1,5-2-5.0-H_1x02_P5.00mm_Horizontal",1,PWR,
J10,"TerminalBlock_Phoenix_PT-1,5-3-5.0-H_1x03_P5.00mm_Horizontal",1,TEMP_SENSOR,
J11,"TerminalBlock_Phoenix_PT-1,5-12-5.0-H_1x12_P5.00mm_Horizontal",1,VALVES,
J12,"TerminalBlock_Phoenix_PT-1,5-6-5.0-H_1x06_P5.00mm_Horizontal",1,PHOTOSENSOR,
J13,"TerminalBlock_Phoenix_PT-1,5-2-5.0-H_1x02_P5.00mm_Horizontal",1,PELTIER,
J14,PinHeader_1x05_P2.54mm_Vertical,1,GPIO_INT,
J2,"TerminalBlock_Phoenix_PT-1,5-7-5.0-H_1x07_P5.00mm_Horizontal",1,RAIL1,
J3,"TerminalBlock_Phoenix_PT-1,5-7-5.0-H_1x07_P5.00mm_Horizontal",1,RAIL2,
J4,"TerminalBlock_Phoenix_PT-1,5-7-5.0-H_1x07_P5.00mm_Horizontal",1,RAIL3,
J5,"TerminalBlock_Phoenix_PT-1,5-7-5.0-H_1x07_P5.00mm_Horizontal",1,RAIL4,
J6,"TerminalBlock_Phoenix_PT-1,5-7-5.0-H_1x07_P5.00mm_Horizontal",1,RAIL5,
J7,"TerminalBlock_Phoenix_PT-1,5-7-5.0-H_1x07_P5.00mm_Horizontal",1,RAIL6,
J8,"TerminalBlock_Phoenix_PT-1,5-14-5.0-H_1x14_P5.00mm_Horizontal",1,ARDUINO,
J9,"TerminalBlock_Phoenix_PT-1,5-6-5.0-H_1x06_P5.00mm_Horizontal",1,LED,
"JP1, JP2, JP3, JP4",PinHeader_1x02_P2.54mm_Vertical,4,JUMP,C5305
"L14, L15, L16, L17, L18, L19, L20, L21",L_Cenker_CKST0603,8,15uH 4A,C3002651
"L22, L23",L_SMMS1360,2,100uH,C149534
Q1,TO-263-2,1,LNE08R085,C483709
"R1, R54, R56, R58, R60, R70",0805,6,4.7k,C17673
"R10, R12, R14",0805,3,120k,C17436
"R11, R13, R15",0805,3,200k,C17539
"R16, R2, R21, R22, R23, R24, R25, R26, R27, R3, R4, R5, R6, R7",0805,14,220R,C17557
"R17, R46, R47",0805,3,10K,C17414
"R18, R19",0805,2,30k,C17621
R20,0805,1,150k,C17470
"R28, R29, R30, R31, R32, R33, R42",0805,7,47k 1%,C17713
R44,0805,1,8.87k 1%,C37551
"R48, R50, R53, R55, R57, R59, R61, R63",0805,8,100k 1%,C149504
"R49, R52, R62",0805,3,9.09k 1%,C408923
R51,2512,1,0.005R,C5121085
R64,0805,1,24.9k 1%,C234872
"R65, R66",2512,2,0.15R,C2924565
"R67, R68",2512,2,0.3R,C2912677
R69,0805,1,13k,C217812
"R8, R9",0805,2,1K,C17513
RV1,Potentiometer_Bourns_3296W_Vertical,1,5M,
"RV6, RV7, RV8, RV9",Potentiometer_Bourns_3296W_Vertical,4,47k 10-turn,C83686
SW1,RS 2066972,1,RS 206-6972,
"U1, U2, U3",HTSSOP-14-1EP_4.4x5mm_P0.65mm_EP3.4x5mm_Mask3x3.1mm_ThermalVias,3,DRV104,C2150346
"U10, U11, U6, U7, U8, U9",SOT-353_SC-70-5,6,74LVC1G04,C8207
"U13, U22",CONV_AL8861Y-13,2,AL8861Y-13,C507867
U14,SOT-23-5,1,ZXCT1110,C78482
"U15, U16, U17, U18, U19, U20, U21, U4",Texas_HSOP-8-1EP_3.9x4.9mm_P1.27mm_ThermalVias,8,LMR33630ADDA,C841384
U5,SOIC-8_3.9x4.9mm_P1.27mm,1,MCP6002-xSN,C7377
